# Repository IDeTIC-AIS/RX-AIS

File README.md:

# About this Repository

Within this repository you will find three directories: Firmware, Layout and Technical Notes. The file system repository allows access to files to develop an Automatic Identification System Modular Receiver.

**Firmware**

- aisRxController.ino =>  AIS Firmware  with Arduino language.
- nmea.c              =>  Library to implement the NMEA Protocol.
- nmea.h              =>  Header File.

**Layout**
- ais_rx1_v1.sch      =>  Schematic design in Eagle.
- ais_rx1_v1.brd      =>  Layout design in Eagle.
- AIS_RX_PCB.pdf      =>  Schematic and Layout (top and bottom layers).
- Connections.pdf     =>  Description of pin connections over prototype board.

**TechNotes**
- TechNote1.pdf       =>  RTL-SDR Sensitivity for AIS System.
- TechNote2.pdf       =>  DV-MEGA GMSK bitrate set-up for AIS System.

# Contact:
 
Francisco Cabrera, Nicolás Molina, Víctor Araña

francisco.cabrera@ulpgc.es

DSC-IDeTIC, Pabellón B Telecomunicaciones,

ULPGC, Campus de Tafira S/N,

Las Palmas de G.C. 35011, Spain

Miluse Tichavska

miluse.tichavska@marinetraffic.com

Exmile Solutions Limited (MarineTraffic),

1 Kings Avenue,

London N21 3NA, UK

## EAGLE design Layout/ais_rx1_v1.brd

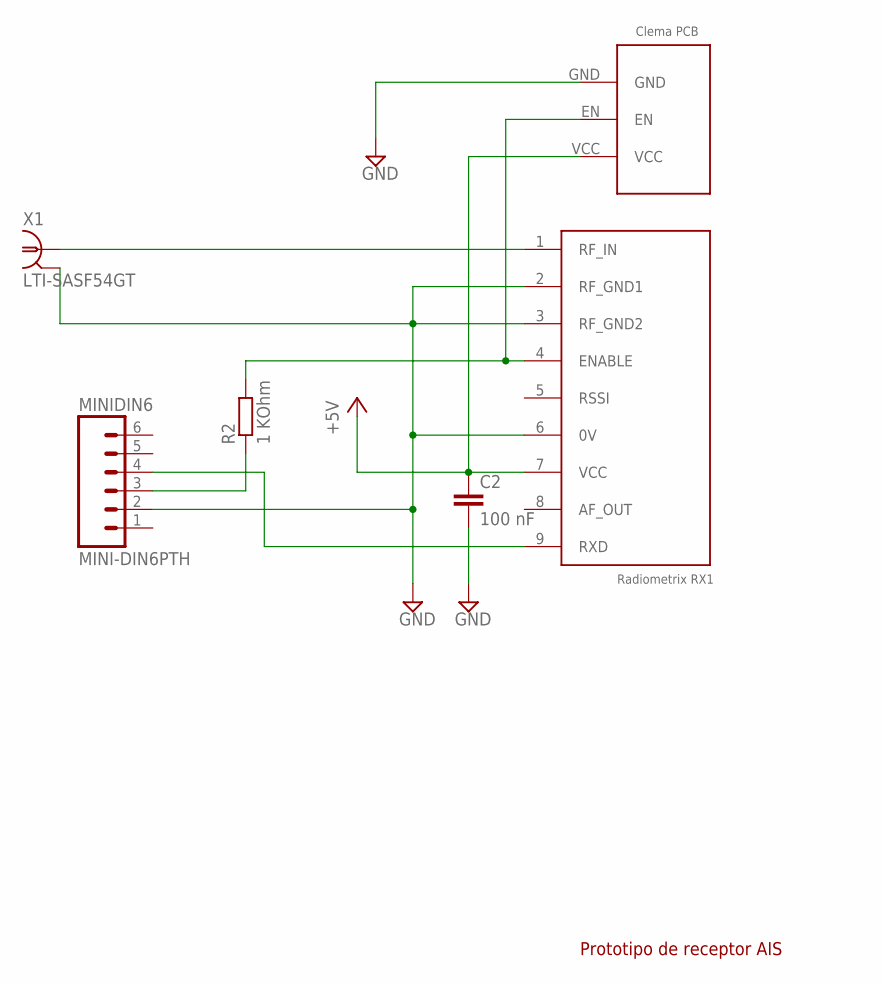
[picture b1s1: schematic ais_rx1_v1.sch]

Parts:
C2: 100 nF; C0805
CLEMAPCB1: CLEMA
MINIDIN6: MINI-DIN6PTH; MINI-DIN6
R2: 1 KOhm; R0805
RX1: RX1
X1: LTI-SASF54GT

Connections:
+5V: C2.1, CLEMAPCB1.VCC, RX1.7 (VCC)
GND: C2.2, CLEMAPCB1.GND, MINIDIN6.2, RX1.2 (RF_GND1), RX1.3 (RF_GND2), RX1.6 (0V), X1.2, X1.3 (2), X1.4 (2), X1.5 (2)
unnamed: RX1.1 (RF_IN), X1.1
unnamed: CLEMAPCB1.EN, R2.2, RX1.4 (ENABLE)
unnamed: MINIDIN6.4, RX1.9 (RXD)
unnamed: MINIDIN6.3, R2.1
RSSI: RX1.5 (RSSI)

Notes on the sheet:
Prototipo de receptor AIS

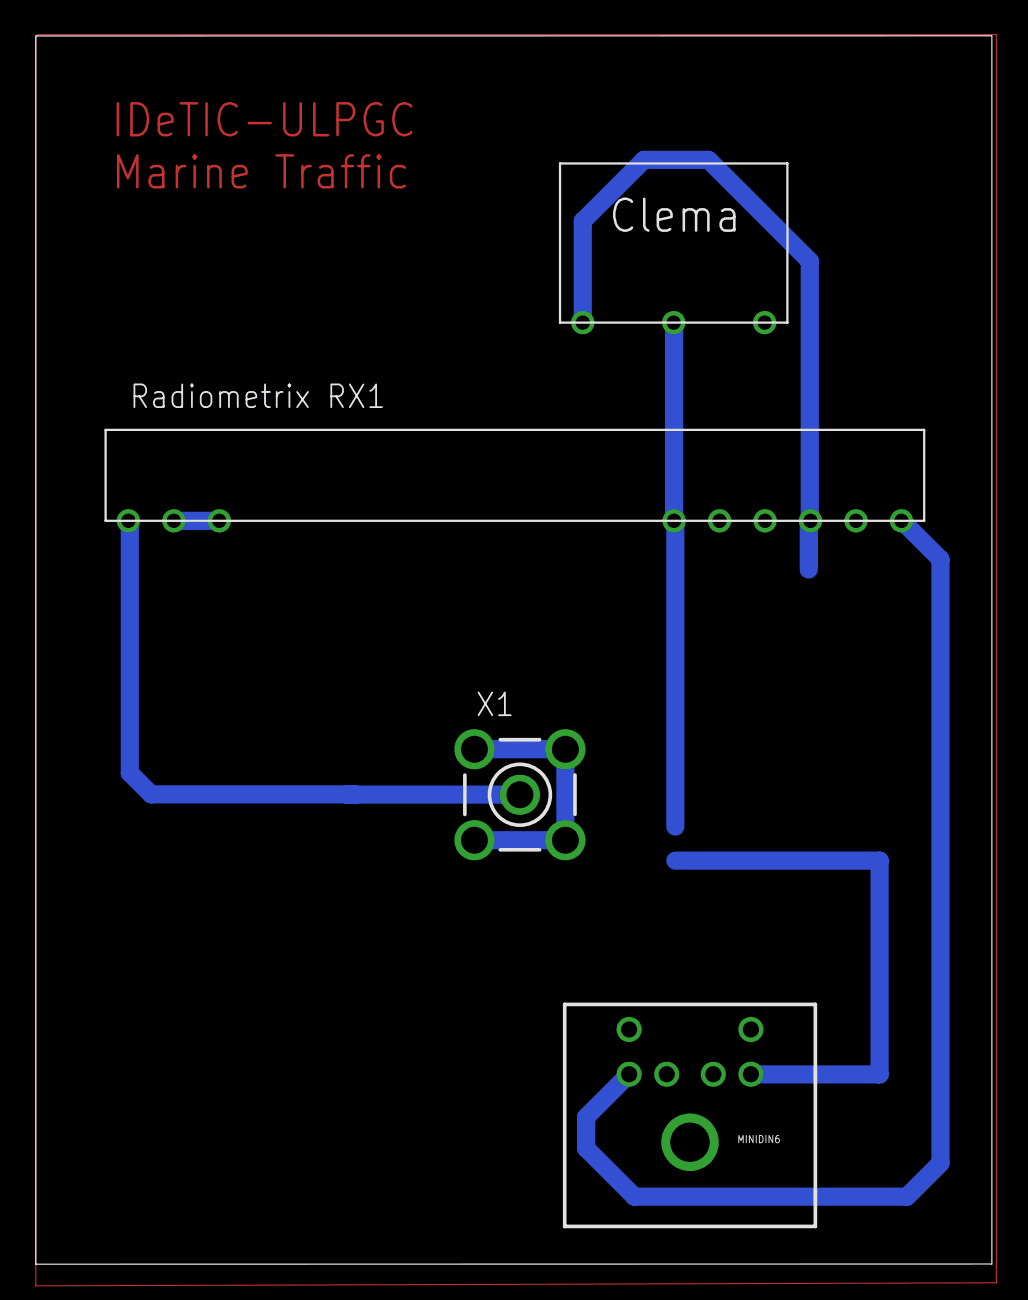
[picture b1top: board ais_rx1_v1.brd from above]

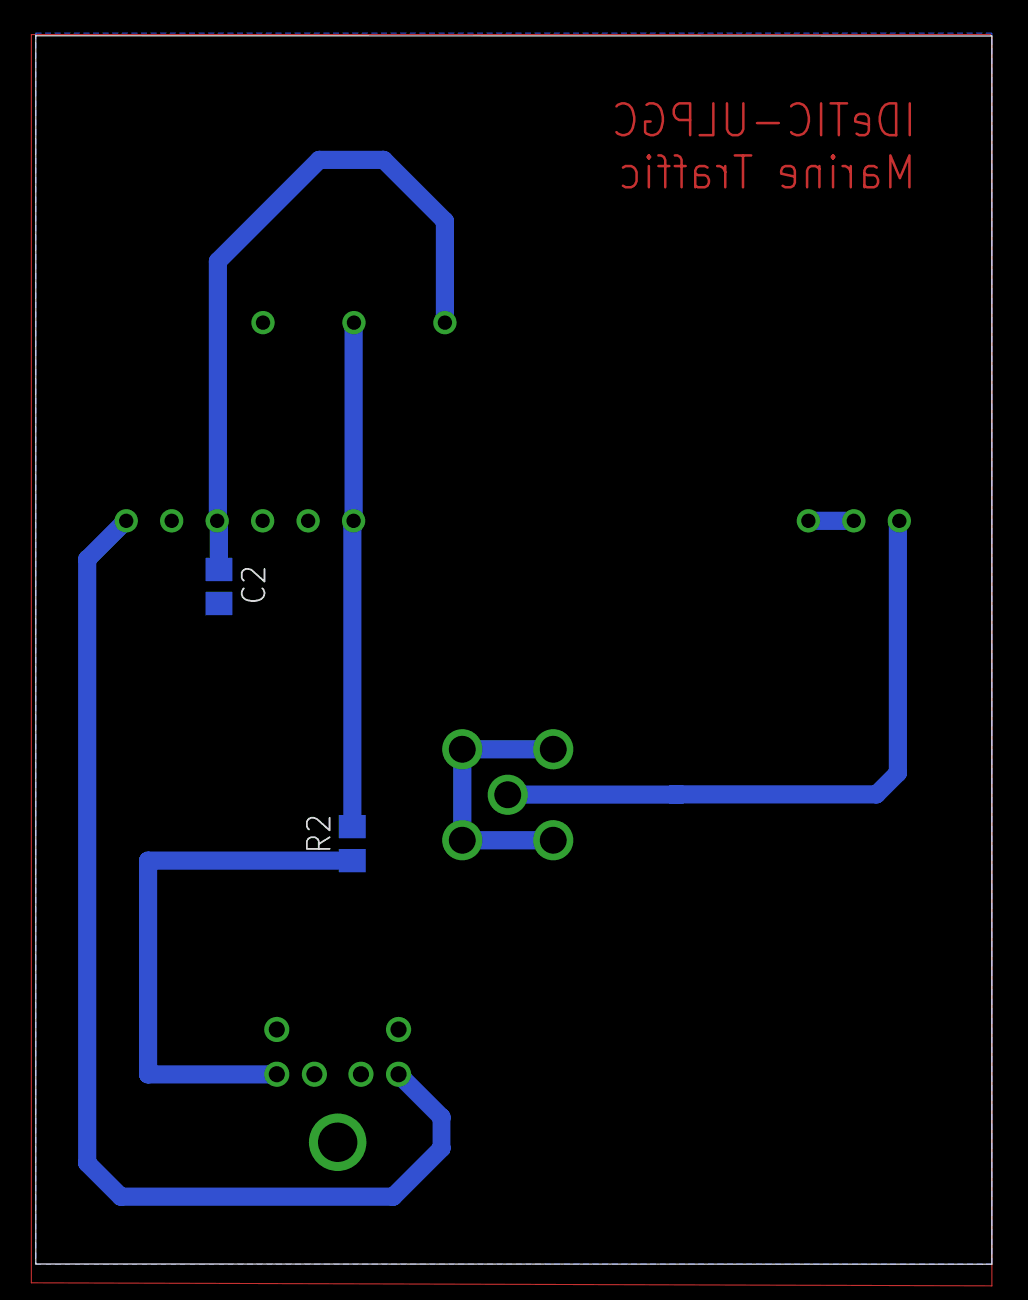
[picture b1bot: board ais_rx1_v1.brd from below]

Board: 2 copper layers, 53.4 x 68.6 mm, 6 parts (2 on the bottom side), 6 nets.

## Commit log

2016-05-24 RX-AIS

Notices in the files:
parts and their libraries:
SparkFun-Connectors: Licensing: CC v3.0 Share-Alike You are welcome to use this library for commercial purposes.
